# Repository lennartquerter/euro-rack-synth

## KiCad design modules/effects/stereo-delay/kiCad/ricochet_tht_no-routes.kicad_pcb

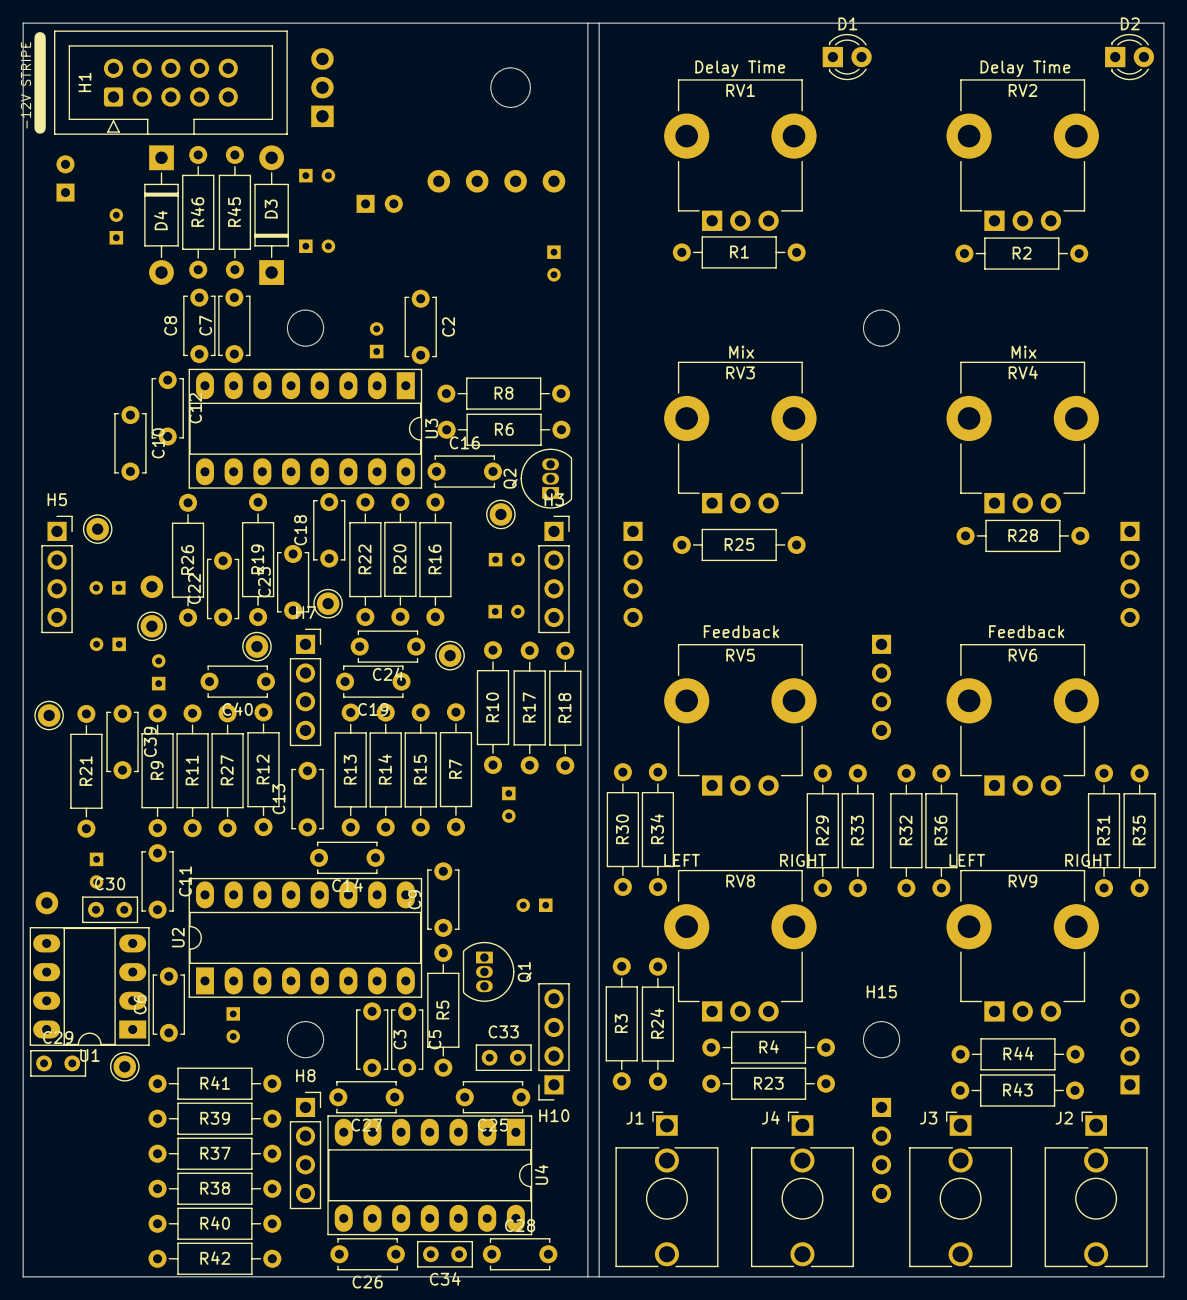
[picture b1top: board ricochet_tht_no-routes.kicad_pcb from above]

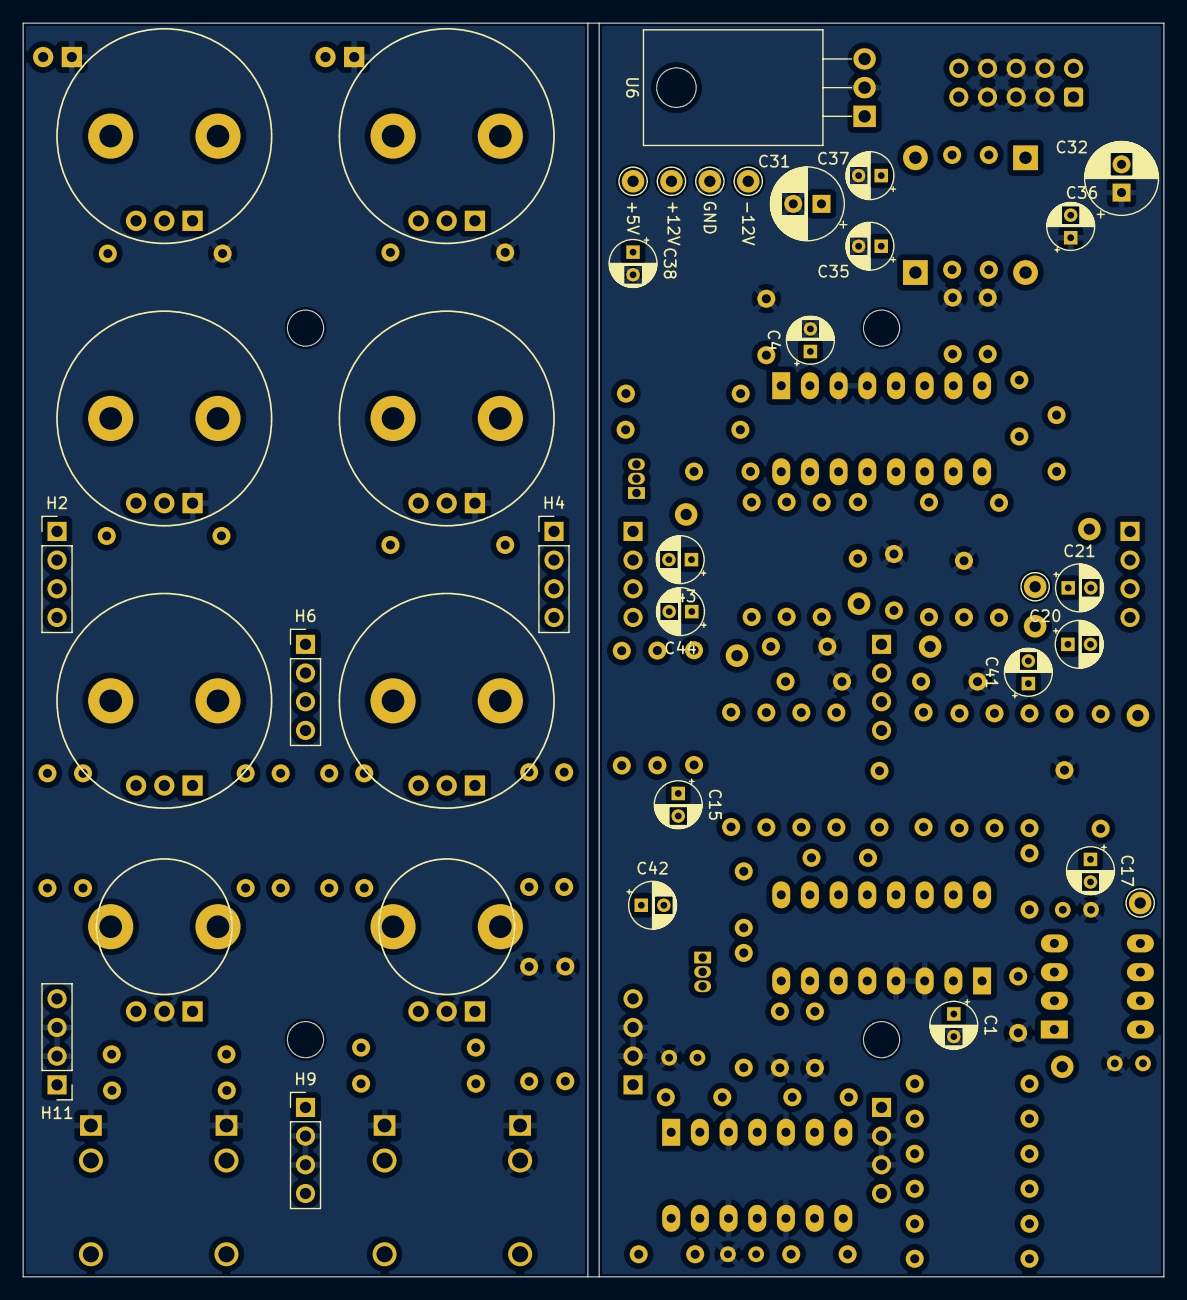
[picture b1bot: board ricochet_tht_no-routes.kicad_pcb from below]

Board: 2 copper layers, 101.0 x 111.0 mm, 142 parts (28 on the bottom side), 96 nets, no tracks yet.

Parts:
C1, C4, C21, C41, C42, C43: 10uF; CP_Radial_D4.0mm_P2.00mm
C2, C3, C5, C6, C7, C8, C9, C10, C12, C14: 100nF; C_Disc_D5.0mm_W2.5mm_P5.00mm
C11, C13, C16, C18: 560pF; C_Disc_D5.0mm_W2.5mm_P5.00mm
C15, C17, C20, C44: 4.7uF; CP_Radial_D4.0mm_P2.00mm
C19, C22: 3.3nF; C_Disc_D5.0mm_W2.5mm_P5.00mm
C23, C40: 10nF; C_Disc_D5.0mm_W2.5mm_P5.00mm
C24, C39: 3.9nF; C_Disc_D5.0mm_W2.5mm_P5.00mm
C25, C26: 27pF; C_Disc_D5.0mm_W2.5mm_P5.00mm
C27, C28: 47pF; C_Disc_D5.0mm_W2.5mm_P5.00mm
C29, C30, C33, C34: 0.1uF; C_Rect_L4.6mm_W2.0mm_P2.50mm_MKS02_FKP02
C31, C32: 47uF; CP_Radial_D6.3mm_P2.50mm
C35, C36, C37, C38: 0.1uF; CP_Radial_D4.0mm_P2.00mm
D1, D2: LED; LED_D3.0mm
D3, D4: 1N5819; D_DO-41_SOD81_P10.16mm_Horizontal
H1: Conn_02x05_PWR_Eurorack; IDC-Header_2x05_P2.54mm_Vertical
H2, H4, H6, H9, H11: PinHeader_01x04; PinHeader_1x04_P2.54mm_Vertical
H3, H5, H7, H8, H10: PinSocket_01x04; PinSocket_1x04_P2.54mm_Vertical
H12, H13, H14, H15: MountingHole; MountingHole_3.2mm_M3
J1, J4: INPUT; Jack_3.5mm_QingPu_WQP-PJ398SM_Vertical_CircularHoles
J2: L/MONO_OUTPUT; Jack_3.5mm_QingPu_WQP-PJ398SM_Vertical_CircularHoles
J3: R_OUTPUT; Jack_3.5mm_QingPu_WQP-PJ398SM_Vertical_CircularHoles
Q1, Q2: 2N3904; TO-92_Inline
R1, R2: 2K; R_Default (DIN0207)
R3, R7, R8, R24: 100K; R_Default (DIN0207)
R4, R5, R6, R23, R43, R44: 1K; R_Default (DIN0207)
R9, R11, R14, R15, R16, R17, R22, R25, R26, R28, R29, R30, R31, R32, R33, R34, R35, R36, R39, R40, R41, R42: 10K; R_Default (DIN0207)
R10, R13, R20, R21: 15K; R_Default (DIN0207)
R12, R19: 5.6K; R_Default (DIN0207)
R18, R27: 4.7K; R_Default (DIN0207)
R37, R38: 33K; R_Default (DIN0207)
R45, R46: 10R; R_Default (DIN0207)
RV1, RV2: B50K; Potentiometer_TT_P0915N
RV3, RV4, RV5, RV6: B100K; Potentiometer_TT_P0915N
RV8, RV9: B25K; Potentiometer_TT_P0915N
TP1: +12V; Pin_D1.0mm_L10.0mm
TP2: GND; Pin_D1.0mm_L10.0mm
TP3: -12V; Pin_D1.0mm_L10.0mm
TP4: INPUT_CH_1; Pin_D1.0mm_L10.0mm
TP5: INPUT_CH_2; Pin_D1.0mm_L10.0mm
TP6: OUTPUT_CH_1; Pin_D1.0mm_L10.0mm
TP7: OUTPUT_CH_2; Pin_D1.0mm_L10.0mm
TP8: DELAY_TIME_CH_2; Pin_D1.0mm_L10.0mm
TP9: DELAY_TIME_CH_1; Pin_D1.0mm_L10.0mm
TP10: POST_FEEDBACK_CH_2; Pin_D1.0mm_L10.0mm
TP11: POST_FEEDBACK_CH_1; Pin_D1.0mm_L10.0mm
TP12: MIX_INPUT_CH_2; Pin_D1.0mm_L10.0mm
TP13: MIX_INPUT_CH_1; Pin_D1.0mm_L10.0mm
TP14: +5V; Pin_D1.0mm_L10.0mm
U1: TL072; DIP-8_W7.62mm_Socket_LongPads
U2, U3: PT2399; DIP-16_W7.62mm_Socket_LongPads
U4: TL074; DIP-14_W7.62mm_Socket_LongPads
U6: L7805; TO-220-3_Horizontal_TabDown

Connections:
+5V: C2.2, C6.2, C38.1, TP14.1, U2.1 (VCC), U3.1 (VCC), U6.3 (OUT)
+12V: C29.1, C31.1, C33.1, C35.1, C37.1, R7.2, R8.2, R45.2, TP1.1, U1.8 (V+), U4.4 (V+), U6.1 (IN)
-12V: C30.2, C32.2, C34.2, C36.2, R46.2, TP3.1, U1.4 (V-), U4.11 (V-)
/PT2399_delay-module_channel_1/delay_input: C15.2, TP4.1, U1.1, U1.2 (-)
/PT2399_delay-module_channel_1/delay_output: C42.2, H7.2, TP6.1
/PT2399_delay-module_channel_2/delay_input: C17.2, TP5.1, U1.6 (-), U1.7
/PT2399_delay-module_channel_2/delay_output: C41.2, H7.1, TP7.1
GNDREF: C1.2, C2.1, C3.2, C4.2, C5.2, C6.1, C7.2, C8.2, C19.2, C22.2, C23.2, C24.2, C29.2, C30.1, C31.2, C32.1, C33.2, C34.1, C35.2, C36.1, C37.2, C38.2, C39.2, C40.2, D1.1 (K), D2.1 (K), H1.3, H1.4, H1.5, H1.6, H1.7, H1.8, H8.2, H8.3, H9.2, H9.3, H10.2, H10.3, H11.2, H11.3, J1.S, J1.TN, J2.S, J3.S, J4.S, R1.1, R2.1, R3.1, R24.1, RV3.1, RV4.1, RV8.2, RV9.2, TP2.1, U2.3 (AGND), U2.4 (DGND), U3.3 (AGND), U3.4 (DGND), U4.3 (+), U4.5 (+), U4.10 (+), U4.12 (+), U6.2 (GND)
unnamed: C15.1, R10.1
unnamed: C17.1, R21.1
unnamed: C19.1, R13.2, R14.2, R15.2
unnamed: C20.1, C39.1, R9.2, R11.2, R21.2, TP10.1
unnamed: C21.1, C40.1, R12.2, TP12.1
unnamed: C22.1, R20.2, R22.2, R26.2
unnamed: C23.1, C43.1, R19.2, TP13.1
unnamed: C24.1, C44.1, R10.2, R16.2, R17.2, TP11.1
unnamed: C25.2, R37.2, R39.1, U4.1
unnamed: C26.2, R38.2, R40.1, U4.8
unnamed: C41.1, R27.2
unnamed: C42.1, R18.2
unnamed: D1.2 (A), H4.2
unnamed: D2.2 (A), H2.2
unnamed: D3.2 (A), H1.9, H1.10
unnamed: D3.1 (K), R45.1
unnamed: D4.2 (A), R46.1
unnamed: D4.1 (K), H1.1, H1.2
unnamed: H2.1, RV2.1
unnamed: H2.3, RV4.3
unnamed: H2.4, RV6.2
unnamed: H3.1, TP9.1, U3.6 (VCO)
unnamed: H3.2, Q2.1 (E)
unnamed: C43.2, H3.3
unnamed: C44.2, H3.4
unnamed: H4.1, RV1.1
unnamed: H4.3, RV3.3
unnamed: H4.4, RV5.2
unnamed: H5.1, TP8.1, U2.6 (VCO)
unnamed: H5.2, Q1.1 (E)
unnamed: C21.2, H5.3
unnamed: C20.2, H5.4
unnamed: H6.1, R31.1, R32.1
unnamed: H6.2, R29.1, R30.1
unnamed: H6.3, R34.2, R36.2
unnamed: H6.4, R33.2, R35.2
unnamed: C26.1, H7.3, R38.1, U4.9 (-)
unnamed: C25.1, H7.4, R37.1, U4.2 (-)
unnamed: H8.1, U1.3 (+)
unnamed: H8.4, U1.5 (+)
unnamed: H9.1, R4.1
unnamed: H9.4, R23.1
unnamed: C27.2, H10.1, R41.2, U4.7
unnamed: C28.2, H10.4, R42.2, U4.14
unnamed: H11.1, R43.2
unnamed: H11.4, R44.2
unnamed: J1.T, J4.TN, R3.2, R4.2
unnamed: J2.T, J3.TN, R43.1
unnamed: J3.T, R44.1
unnamed: J4.T, R23.2, R24.2
unnamed: Q1.2 (B), R5.2
unnamed: Q1.3 (C), R7.1
unnamed: Q2.2 (B), R6.2
unnamed: Q2.3 (C), R8.1
unnamed: R1.2, RV1.2, RV1.3
unnamed: R2.2, RV2.2, RV2.3
unnamed: R25.1, RV5.3
unnamed: R25.2, RV3.2
unnamed: R28.1, RV6.3
unnamed: R28.2, RV4.2
unnamed: R29.2, R33.1, RV8.3
unnamed: R30.2, R34.1, RV8.1
unnamed: R31.2, R35.1, RV9.3
unnamed: R32.2, R36.1, RV9.1
unnamed: C5.1, R5.1, U2.8 (CC0)
unnamed: C3.1, U2.7 (CC1)
unnamed: C11.1, R9.1, U2.16 (LPF1-IN)
unnamed: C11.2, R11.1, R27.1, U2.15 (LPF1-OUT)
unnamed: C13.2, R14.1, U2.13 (LPF2-IN)
unnamed: C13.1, R12.1, R13.1, U2.14 (LPF2-OUT)
unnamed: C9.1, U2.10 (OP1-IN)
unnamed: C9.2, U2.9 (OP1-OUT)
unnamed: C14.1, U2.11 (OP2-IN)
unnamed: C14.2, R15.1, U2.12 (OP2-OUT)
unnamed: C1.1, U2.2 (REF)
unnamed: C8.1, R6.1, U3.8 (CC0)
unnamed: C7.1, U3.7 (CC1)
unnamed: C16.1, R16.1, U3.16 (LPF1-IN)
unnamed: C16.2, R17.1, R18.1, U3.15 (LPF1-OUT)
unnamed: C18.2, R22.1, U3.13 (LPF2-IN)
unnamed: C18.1, R19.1, R20.1, U3.14 (LPF2-OUT)
unnamed: C12.1, U3.10 (OP1-IN)
unnamed: C12.2, U3.9 (OP1-OUT)
unnamed: C10.1, U3.11 (OP2-IN)
unnamed: C10.2, R26.1, U3.12 (OP2-OUT)
unnamed: C4.1, U3.2 (REF)
unnamed: C27.1, R39.2, R41.1, U4.6 (-)
unnamed: C28.1, R40.2, R42.1, U4.13 (-)

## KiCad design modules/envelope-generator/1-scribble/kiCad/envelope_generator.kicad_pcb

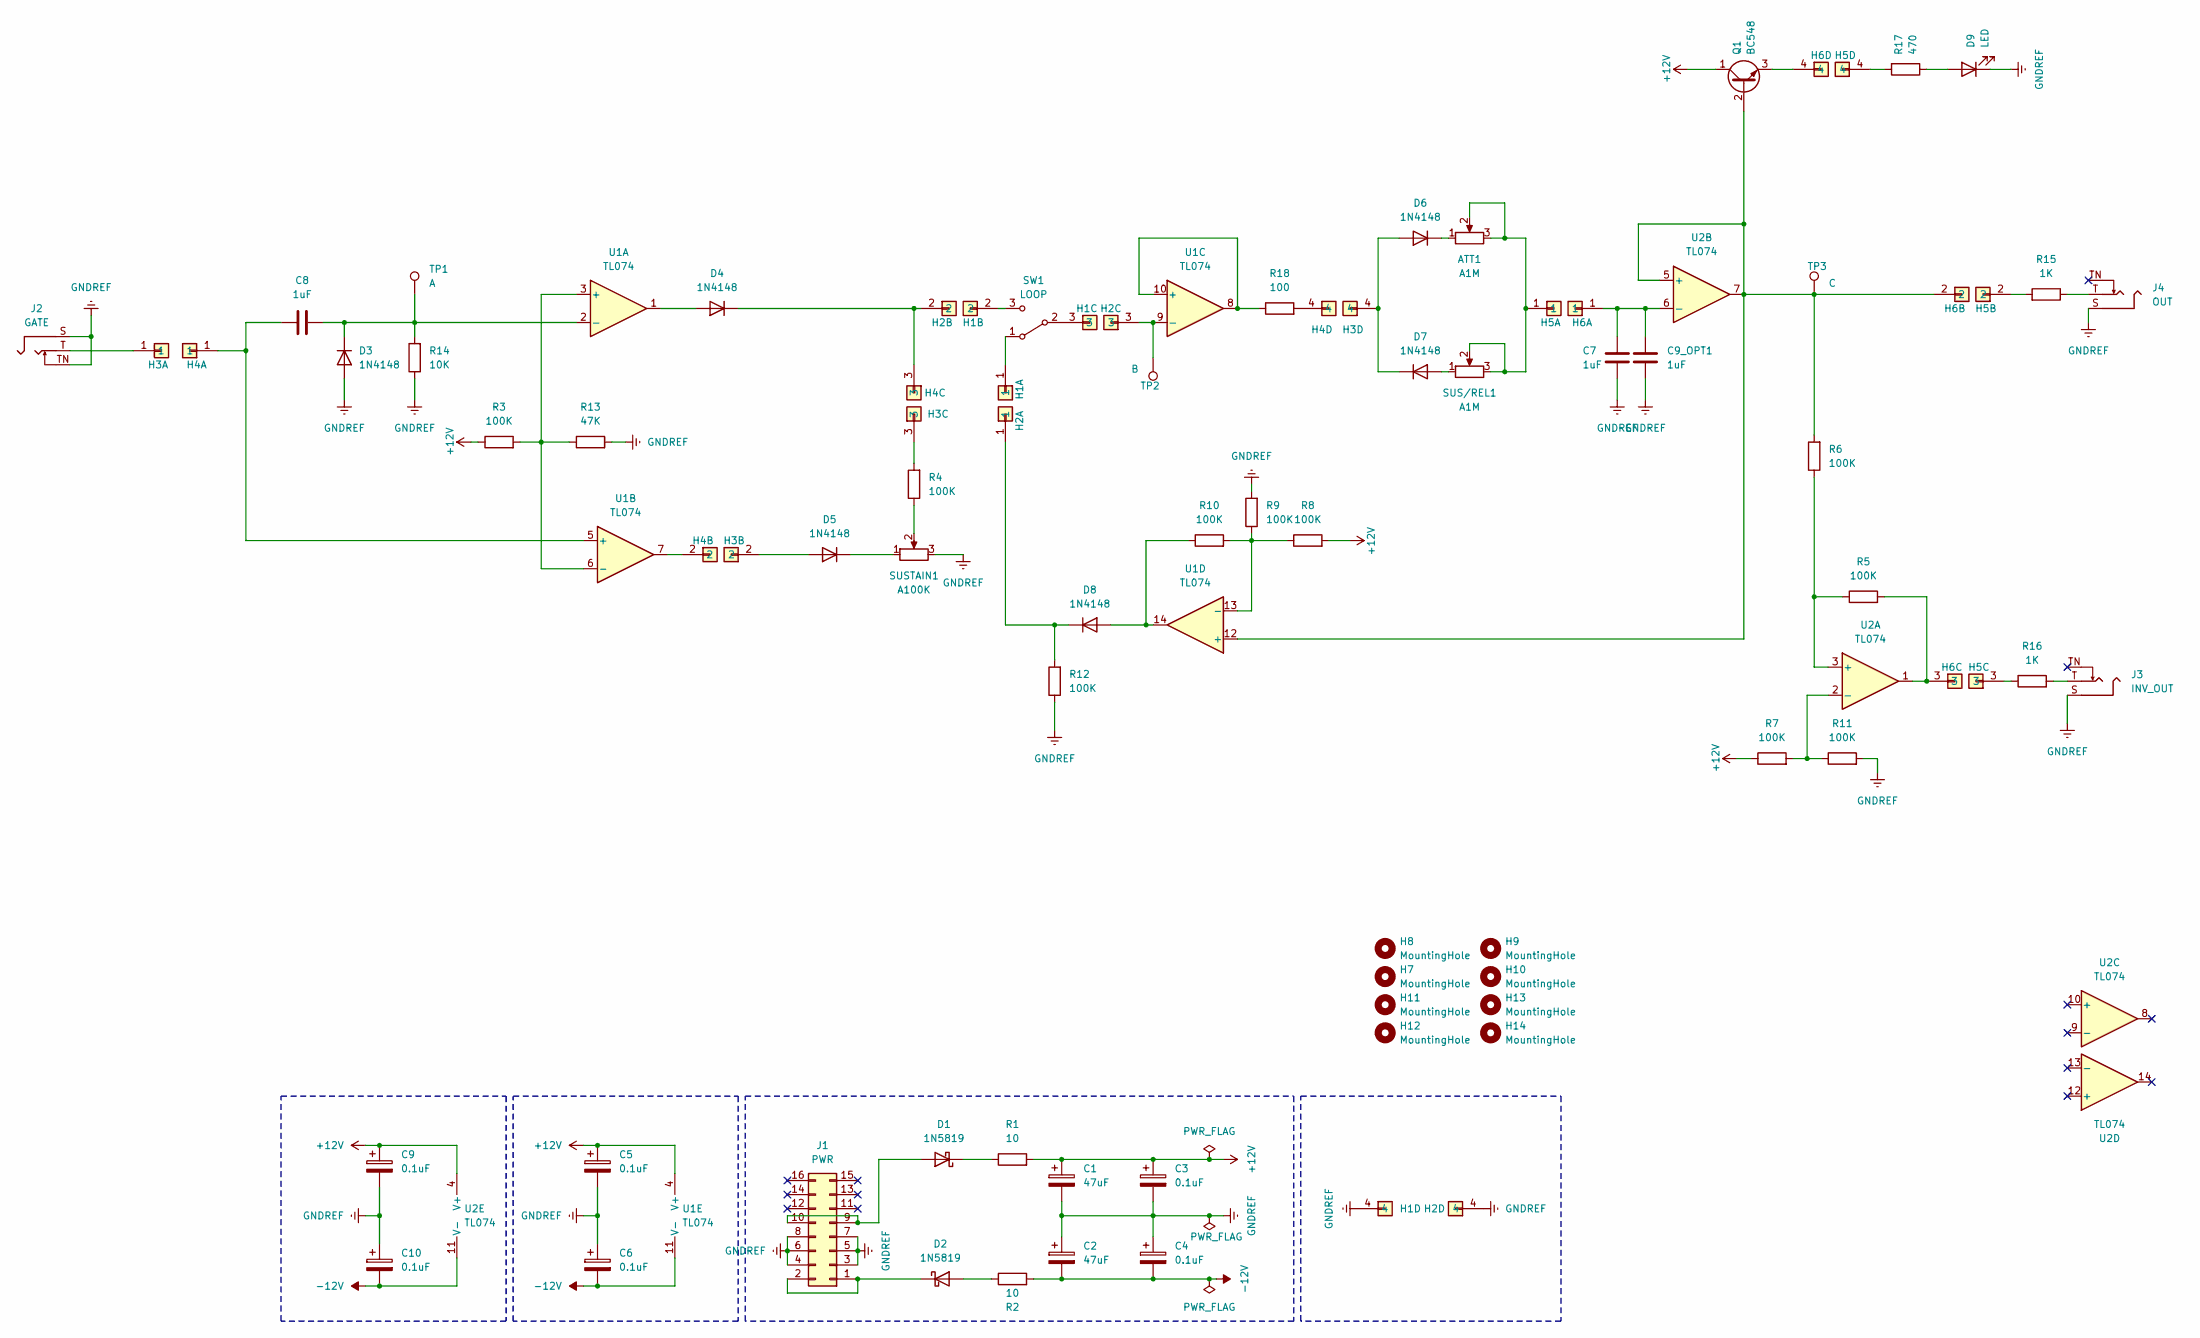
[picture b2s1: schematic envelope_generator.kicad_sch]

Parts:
ATT1: A1M; Potentiometer_TT_P0915N
C1, C2: 47uF; CP_Radial_D6.3mm_P2.50mm
C3, C4, C5, C6, C9, C10: 0.1uF; CP_Radial_D4.0mm_P2.00mm
C7, C8, C9_OPT1: 1uF; C_RECT_MKT_1uF
D1, D2: 1N5819; D_DO-41_SOD81_P10.16mm_Horizontal
D3, D4, D5, D6, D7, D8: 1N4148; D_DO-35_SOD27_P7.62mm_Horizontal
D9: LED; LED_D3.0mm
H1: PinHeader_1x04_P2.00mm_Vertical
H2: PinSocket_1x04_P2.00mm_Vertical
H3: TOP_8_SGL; PinHeader_1x04_P2.00mm_Vertical
H4, H6: BTM_8_SGL; PinSocket_1x04_P2.00mm_Vertical
H5: BTM_8_SGL; PinHeader_1x04_P2.00mm_Vertical
H7, H8, H9, H10, H11, H12, H13, H14: MountingHole; MountingHole_2.5mm
J1: PWR; CONN_02x08_PWR
J2: GATE; Jack_3.5mm_QingPu_WQP-PJ398SM_Vertical_CircularHoles
J3: INV_OUT; Jack_3.5mm_QingPu_WQP-PJ398SM_Vertical_CircularHoles
J4: OUT; Jack_3.5mm_QingPu_WQP-PJ398SM_Vertical_CircularHoles
Q1: BC548; TO-92_Inline
R1, R2: 10; R_Axial_DIN0207_L6.3mm_D2.5mm_P7.62mm_Horizontal
R3, R4, R5, R6, R7, R8, R9, R10, R11, R12: 100K; R_Axial_DIN0207_L6.3mm_D2.5mm_P7.62mm_Horizontal
R13: 47K; R_Axial_DIN0207_L6.3mm_D2.5mm_P7.62mm_Horizontal
R14: 10K; R_Axial_DIN0207_L6.3mm_D2.5mm_P7.62mm_Horizontal
R15, R16: 1K; R_Axial_DIN0207_L6.3mm_D2.5mm_P7.62mm_Horizontal
R17: 470; R_Axial_DIN0207_L6.3mm_D2.5mm_P7.62mm_Horizontal
R18: 100; R_Axial_DIN0207_L6.3mm_D2.5mm_P7.62mm_Horizontal
SUS/REL1: A1M; Potentiometer_TT_P0915N
SUSTAIN1: A100K; Potentiometer_TT_P0915N
SW1: LOOP; SPDT_Toggle
TP1: A
TP2: B
TP3: C
U1, U2: TL074; DIP-14_W7.62mm_Socket_LongPads

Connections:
+12V: C1.1, C3.1, C5.1, C9.1, Q1.1 (C), R1.2, R3.1, R7.1, R8.2, U1.4 (V+), U2.4 (V+)
-12V: C2.2, C4.2, C6.2, C10.2, R2.2, U1.11 (V-), U2.11 (V-)
GNDREF: C1.2, C2.1, C3.2, C4.1, C5.2, C6.1, C7.2, C9.2, C9_OPT1.2, C10.1, D3.2 (A), D9.1 (K), H1.4, H2.4, J1.3 (GND), J1.4 (GND), J1.5 (GND), J1.6 (GND), J1.7 (GND), J1.8 (GND), J2.S, J2.TN, J3.S, J4.S, R9.2, R11.2, R12.1, R13.2, R14.1, SUSTAIN1.3
unnamed: ATT1.2, ATT1.3, H5.1, SUS/REL1.2, SUS/REL1.3
unnamed: D1.2 (A), J1.9 (+12V), J1.10 (+12V)
unnamed: D1.1 (K), R1.1
unnamed: D2.2 (A), R2.1
unnamed: D2.1 (K), J1.1 (-12V), J1.2 (-12V)
unnamed: C8.2, D3.1 (K), R14.2, TP1.1, U1.2 (-)
unnamed: D4.2 (A), U1.1
unnamed: D4.1 (K), H2.2, H4.3
unnamed: D5.2 (A), H3.2
unnamed: D5.1 (K), SUSTAIN1.1
unnamed: D6.2 (A), D7.1 (K), H3.4
unnamed: ATT1.1, D6.1 (K)
unnamed: D7.2 (A), SUS/REL1.1
unnamed: D8.2 (A), R10.1, U1.14
unnamed: D8.1 (K), H2.1, R12.2
unnamed: D9.2 (A), R17.1
unnamed: H3.1, J2.T
unnamed: H3.3, R4.2
unnamed: H4.2, U1.7
unnamed: H4.4, R18.2
unnamed: H5.2, R15.2
unnamed: H5.3, R16.1
unnamed: H5.4, R17.2
unnamed: H6.3, R5.2, U2.1
unnamed: J3.T, R16.2
unnamed: J4.T, R15.1
unnamed: H6.2, Q1.2 (B), R6.2, TP3.1, U1.12 (+), U2.5 (+), U2.7
unnamed: H6.4, Q1.3 (E)
unnamed: R4.1, SUSTAIN1.2
unnamed: H1.1, SW1.1 (A)
unnamed: H1.3, SW1.2 (B)
unnamed: H1.2, SW1.3 (C)
unnamed: R3.2, R13.1, U1.3 (+), U1.6 (-)
unnamed: C8.1, H4.1, U1.5 (+)
unnamed: R18.1, U1.8, U1.10 (+)
unnamed: H2.3, TP2.1, U1.9 (-)
unnamed: R8.1, R9.1, R10.2, U1.13 (-)
unnamed: R5.1, R6.1, U2.3 (+)
unnamed: R7.2, R11.1, U2.2 (-)
unnamed: C7.1, C9_OPT1.1, H6.1, U2.6 (-)

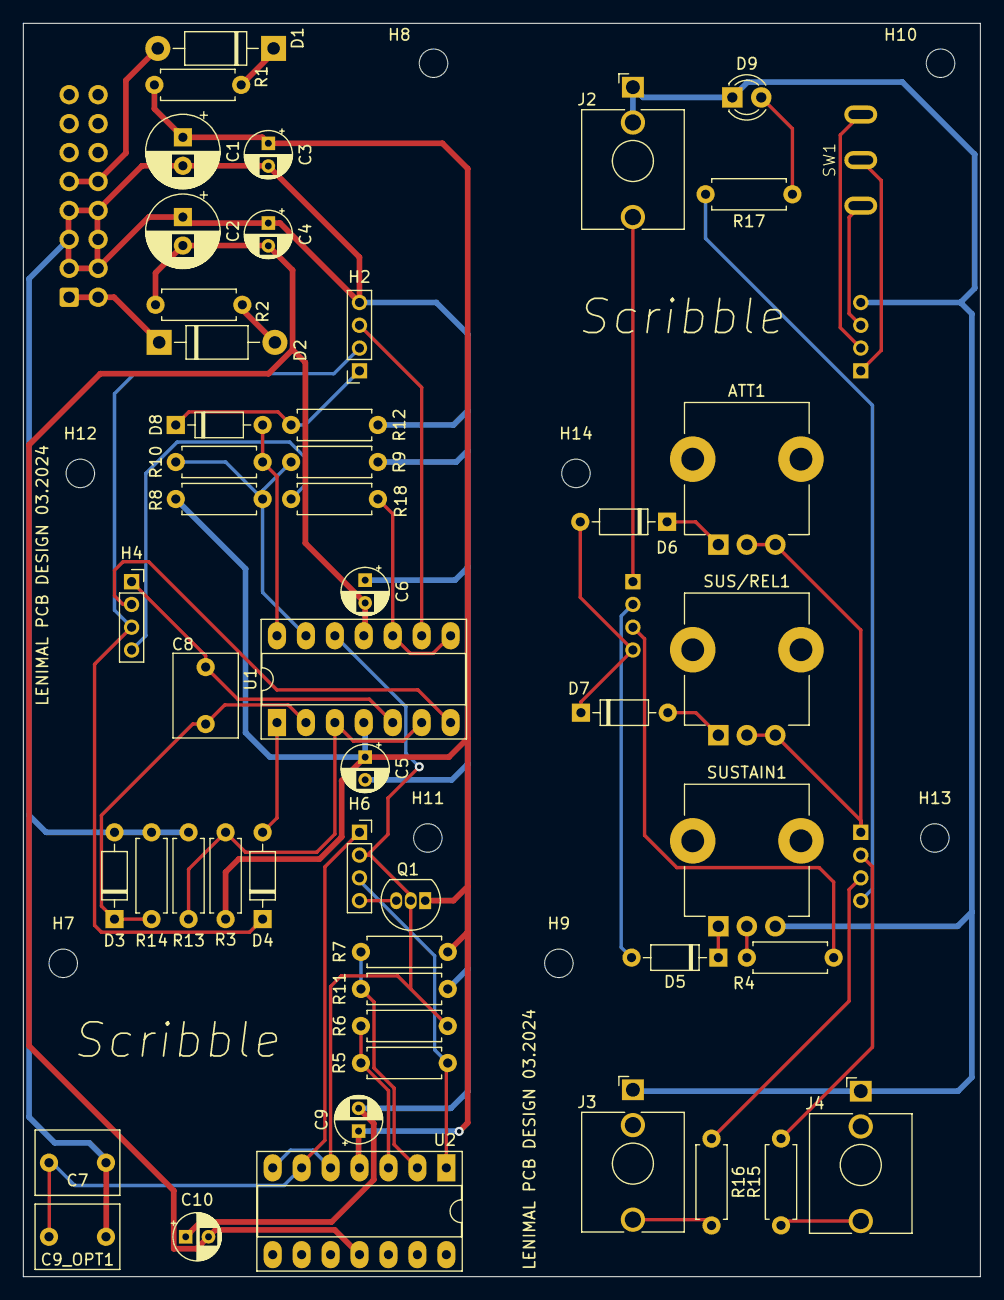
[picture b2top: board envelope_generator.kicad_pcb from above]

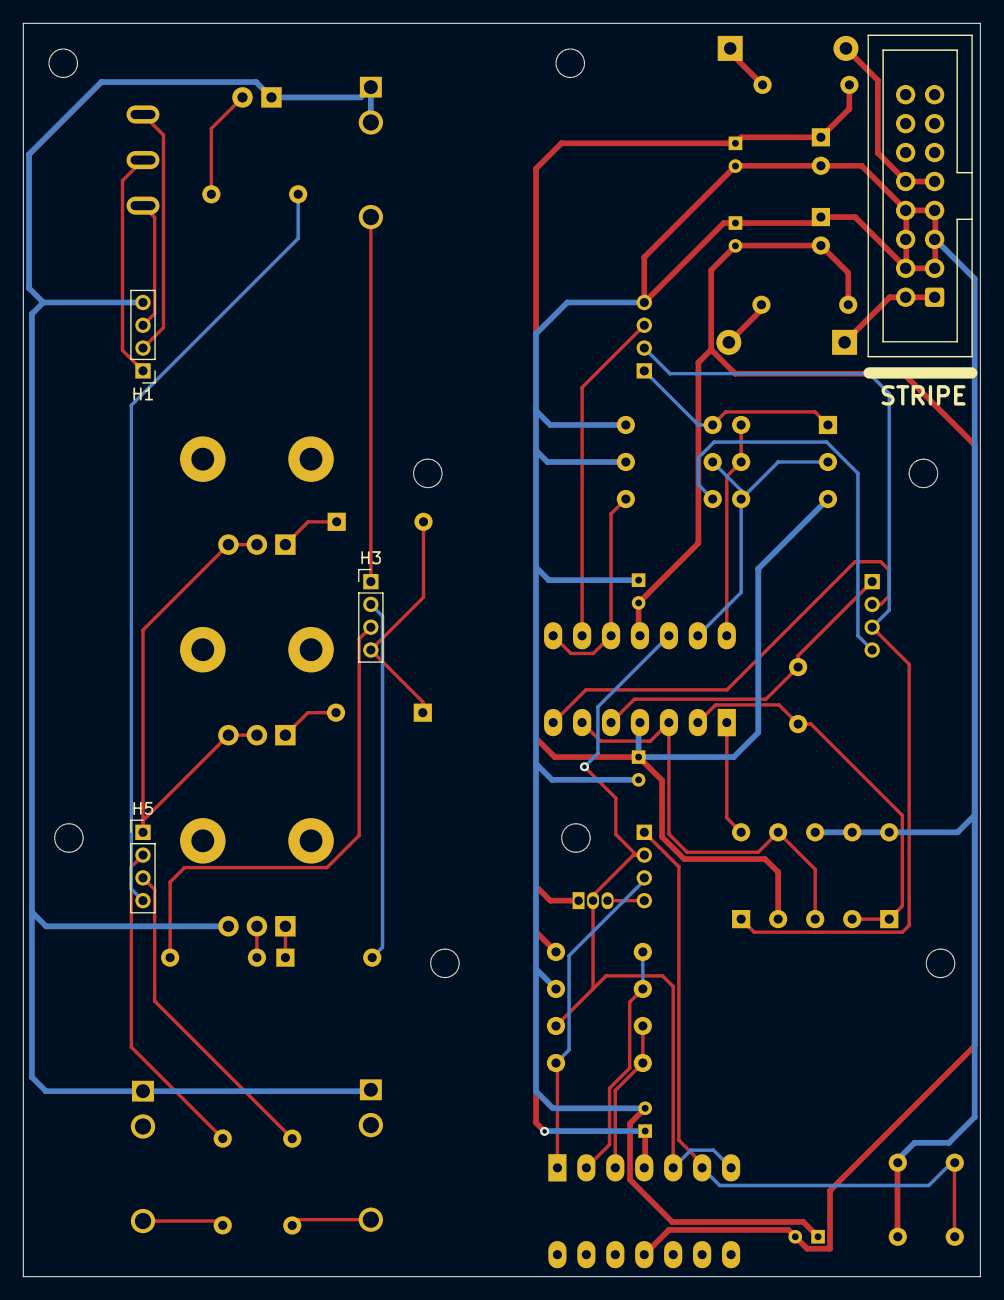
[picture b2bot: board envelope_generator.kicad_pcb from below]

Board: 2 copper layers, 84.0 x 110.0 mm, 63 parts (4 on the bottom side), 43 nets.

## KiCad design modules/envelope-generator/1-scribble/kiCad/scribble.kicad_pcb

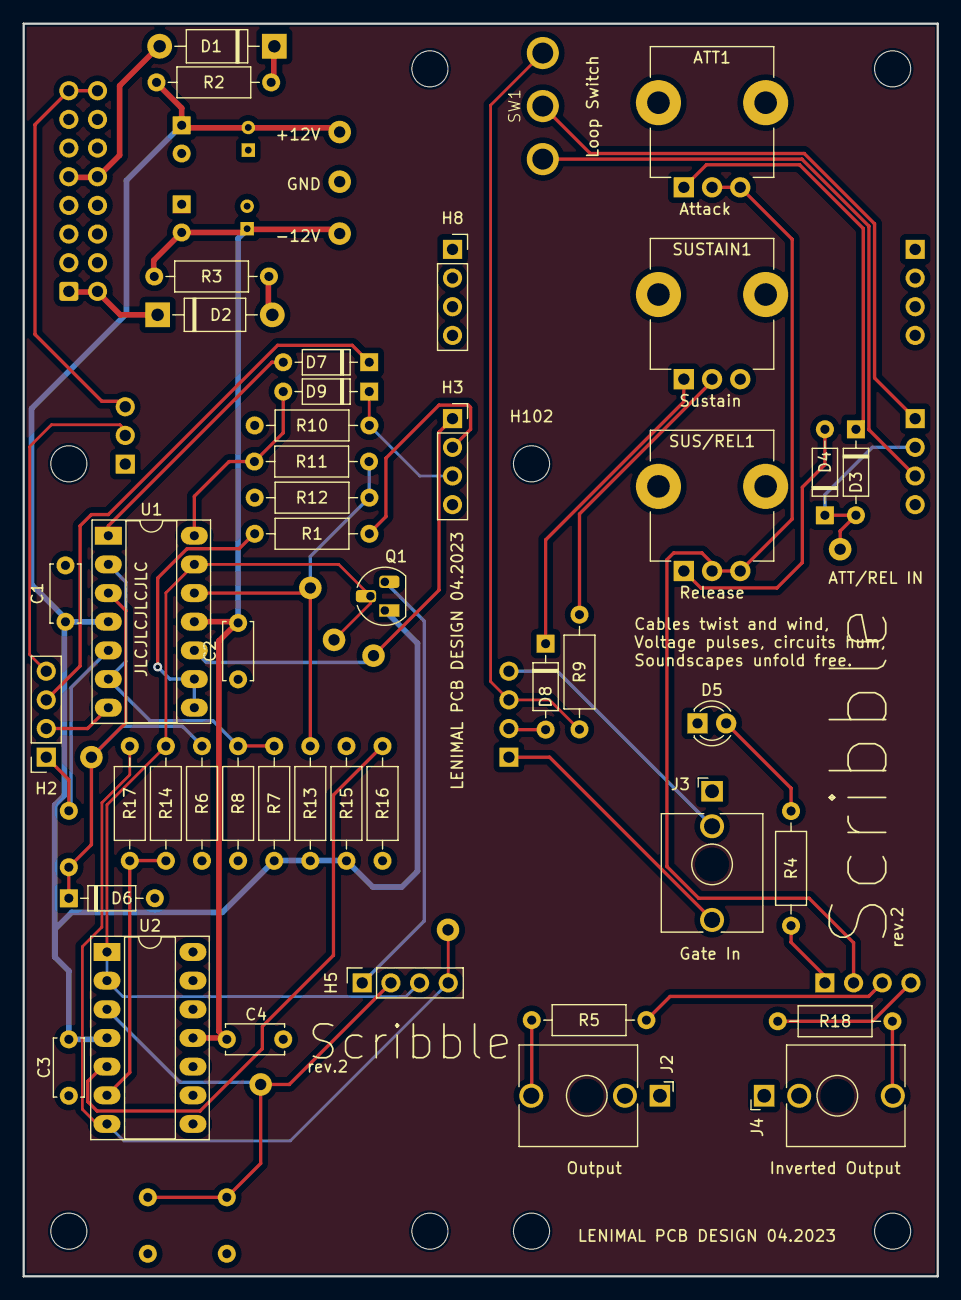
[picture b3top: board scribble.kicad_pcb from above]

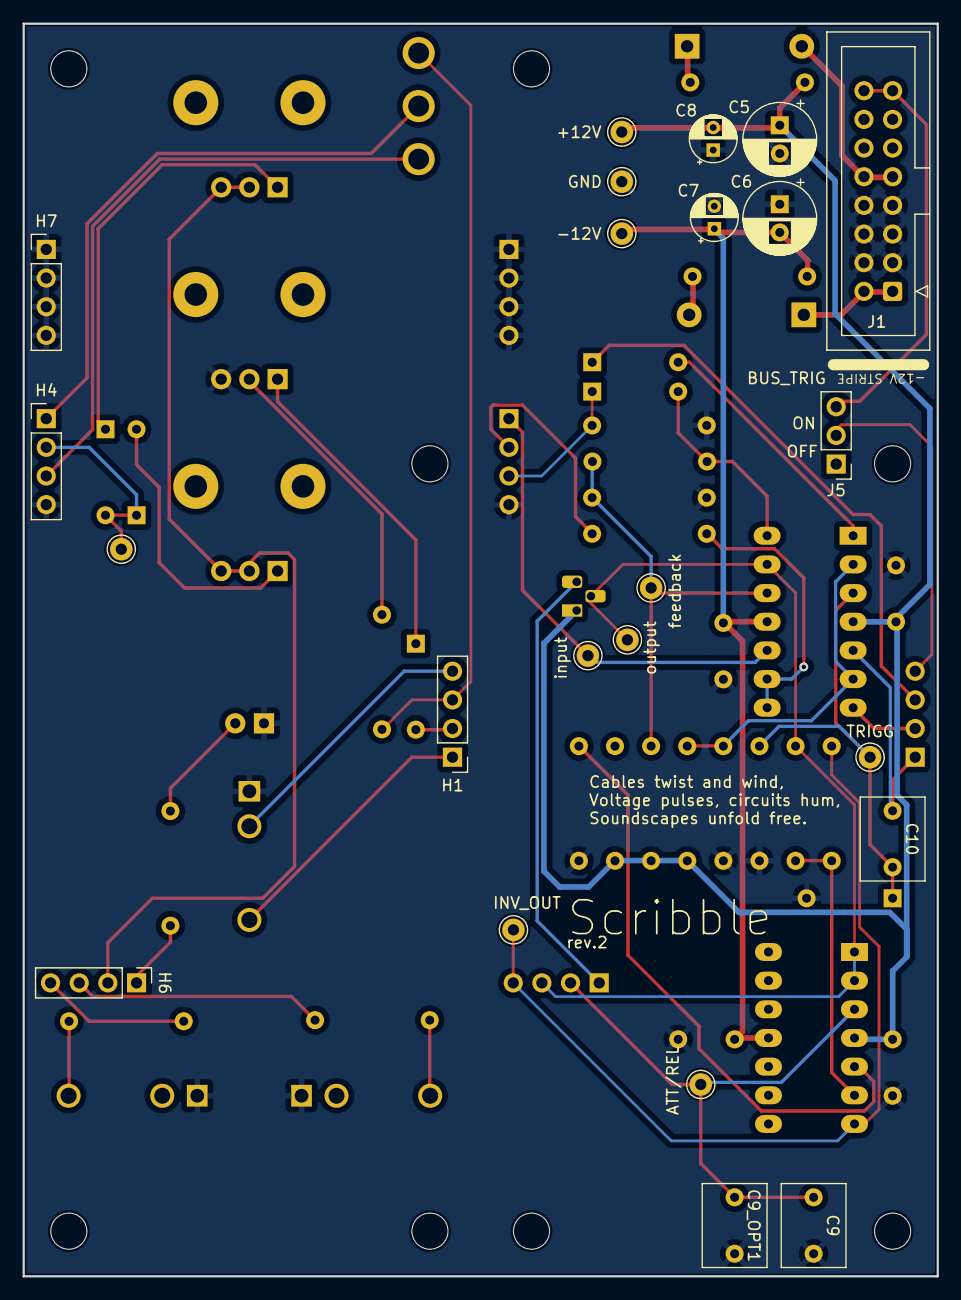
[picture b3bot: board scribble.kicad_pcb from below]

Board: 2 copper layers, 81.0 x 111.0 mm, 76 parts (23 on the bottom side), 45 nets.

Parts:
ATT1: A1M; Potentiometer_TT_P0915N
C1, C2, C3, C4: 0.1uF; C_Disc_D5.0mm_W2.5mm_P5.00mm
C5, C6: 47uF; CP_Radial_D6.3mm_P2.50mm
C7, C8: 0.1uF; CP_Radial_D4.0mm_P2.00mm
C9, C9_OPT1, C10: 1uF; C_RECT_MKT_1uF
D1, D2: 1N5819; D_DO-41_SOD81_P10.16mm_Horizontal
D3, D4, D6, D7, D8, D9: 1N4148; D_DO-35_SOD27_P7.62mm_Horizontal
D5: LED; LED_D3.0mm
H1, H4, H6, H7: PinHeader_1x04; PinHeader_1x04_P2.54mm_Vertical
H2, H3, H5, H8: PinSocket_1x04; PinSocket_1x04_P2.54mm_Vertical
H100, H102, H103, H104, H105, H106, H107, H108: MountingHole; MountingHole_3.2mm_M3
J1: PWR; IDC-Header_2x08_P2.54mm_Vertical
J2: OUT; Jack_3.5mm_QingPu_WQP-PJ398SM_Vertical_CircularHoles
J3: GATE; Jack_3.5mm_QingPu_WQP-PJ398SM_Vertical_CircularHoles
J4: INV_OUT; Jack_3.5mm_QingPu_WQP-PJ398SM_Vertical_CircularHoles
J5: PinHeader_1x03; PinHeader_1x03_P2.54mm_Vertical
Q1: BC548; TO-92_HandSolder
R1: 100R; R_Default (DIN0207)
R2, R3: 10R; R_Default (DIN0207)
R4: 470R; R_Default (DIN0207)
R5, R18: 1K; R_Default (DIN0207)
R6: 10K; R_Default (DIN0207)
R7, R9, R10, R11, R12, R13, R14, R15, R16, R17: 100K; R_Default (DIN0207)
R8: 47K; R_Default (DIN0207)
SUS/REL1: A1M; Potentiometer_TT_P0915N
SUSTAIN1: A100K; Potentiometer_TT_P0915N
SW1: LOOP; SW_default
TP1: TRG_INPUT; Pin_D1.0mm_L10.0mm
TP2: OUT; Pin_D1.0mm_L10.0mm
TP3: TRG; Pin_D1.0mm_L10.0mm
TP4: FBCK_VD; Pin_D1.0mm_L10.0mm
TP5, TP6, TP7: C; Pin_D1.0mm_L10.0mm
TP8: CAP_OUT; Pin_D1.0mm_L10.0mm
TP9: CAP_IN; Pin_D1.0mm_L10.0mm
TP10: INV_OUT; Pin_D1.0mm_L10.0mm
U1, U2: TL074; DIP-14_W7.62mm_Socket_LongPads

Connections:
+12V: C1.1, C3.1, C5.1, C7.1, Q1.1 (C), R2.1, R7.2, R13.1, R15.2, TP5.1, U1.4 (V+), U2.4 (V+)
-12V: C2.2, C4.2, C6.2, C8.2, R3.1, TP7.1, U1.11 (V-), U2.11 (V-)
/feedback_loop/feedback_input: H5.3, Q1.2 (B), R14.1, TP2.1, U1.13 (-), U2.1, U2.2 (-)
/feedback_loop/feedback_output: D9.1 (K), H3.3, R10.1
/input_sustain/gate_in: H2.4, J5.2
/input_sustain/gate_out: H1.3, R9.1, SW1.3 (C)
/inverted_out/inv_output: H5.4, R17.1, TP10.1, U2.7
GNDREF: C1.2, C2.1, C3.2, C4.1, C5.2, C6.1, C7.2, C8.1, C9.2, C9_OPT1.2, D5.1 (K), D6.2 (A), H3.4, H4.4, H7.1, H7.2, H7.3, H7.4, H8.1, H8.2, H8.3, H8.4, J1.3 (GND), J1.4 (GND), J1.5 (GND), J1.6 (GND), J1.7 (GND), J1.8 (GND), J2.S, J3.S, J4.S, R6.2, R8.1, R10.2, R12.1, R16.1, SUSTAIN1.3, TP6.1
unnamed: D1.2 (A), J1.9 (+12V), J1.10 (+12V)
unnamed: D1.1 (K), R2.2
unnamed: D2.2 (A), R3.2
unnamed: D2.1 (K), J1.1 (-12V), J1.2 (-12V)
unnamed: D3.2 (A), D4.1 (K), H4.2, TP9.1
unnamed: ATT1.1, D3.1 (K)
unnamed: D4.2 (A), SUS/REL1.1
unnamed: D5.2 (A), R4.2
unnamed: C10.2, D6.1 (K), R6.1, TP3.1, U1.3 (+)
unnamed: D7.2 (A), U1.1
unnamed: D7.1 (K), H2.3
unnamed: D8.2 (A), H1.2
unnamed: D8.1 (K), SUSTAIN1.1
unnamed: D9.2 (A), R11.2, U1.14
unnamed: H1.1, J3.T
unnamed: H1.4, J3.TN
unnamed: C10.1, H2.1, U1.5 (+)
unnamed: H2.2, U1.7
unnamed: H3.1, TP1.1, U1.10 (+)
unnamed: H3.2, R1.1
unnamed: H4.1, SW1.2 (B)
unnamed: H4.3, SW1.1 (A)
unnamed: H5.1, Q1.3 (E)
unnamed: C9.1, C9_OPT1.1, H5.2, TP8.1, U2.3 (+)
unnamed: H6.1, R4.1
unnamed: ATT1.2, ATT1.3, H6.2, SUS/REL1.2, SUS/REL1.3
unnamed: H6.3, R5.1
unnamed: H6.4, R18.2
unnamed: J2.T, R5.2
unnamed: J4.T, R18.1
unnamed: J1.15 (GATE), J1.16 (GATE), J5.3
unnamed: R9.2, SUSTAIN1.2
unnamed: R7.1, R8.2, U1.2 (-), U1.6 (-)
unnamed: R1.2, U1.8, U1.9 (-)
unnamed: R11.1, R12.2, R13.2, TP4.1, U1.12 (+)
unnamed: R15.1, R16.2, U2.5 (+)
unnamed: R14.2, R17.2, U2.6 (-)

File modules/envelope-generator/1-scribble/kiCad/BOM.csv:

"Reference","Value","Datasheet","Footprint","Qty","DNP"
"ATT1,SUS/REL1","A1M","~","Synth:Potentiometer_TT_P0915N","2",""
"C1,C2,C3,C4,C7,C8","0.1uF","~","Capacitor_THT:CP_Radial_D4.0mm_P2.00mm","6",""
"C5,C6","47uF","~","Capacitor_THT:CP_Radial_D6.3mm_P2.50mm","2",""
"C9,C9_OPT1,C10","1uF","~","Synth:C_RECT_MKT_1uF","3",""
"D1,D2","1N5819","http://www.vishay.com/docs/88525/1n5817.pdf","Synth:D_DO-41_SOD81_P10.16mm_Horizontal","2",""
"D3,D4,D6,D7,D8,D9","1N4148","https://assets.nexperia.com/documents/data-sheet/1N4148_1N4448.pdf","Synth:D_DO-35_SOD27_P7.62mm_Horizontal","6",""
"D5","LED","~","LED_THT:LED_D3.0mm","1",""
"H1","TOP_IN","~","-- mixed values --","1",""
"H2","BTM_IN","~","-- mixed values --","1",""
"H3","BTM_SW","~","Synth:PinSocket_1x04_P2.54mm_Vertical","1",""
"H4","TOP_SW","~","Synth:PinHeader_1x04_P2.54mm_Vertical","1",""
"H5","BTM_OUT","~","Synth:PinSocket_1x04_P2.54mm_Vertical","1",""
"H6","TOP_OUT","~","Synth:PinHeader_1x04_P2.54mm_Vertical","1",""
"H7","TOP_PWR","~","Synth:PinHeader_1x04_P2.54mm_Vertical","1",""
"H8","BTM_PWR","~","Synth:PinSocket_1x04_P2.54mm_Vertical","1",""
"H100,H102,H103,H104,H105,H106,H107,H108","MountingHole","~","MountingHole:MountingHole_3.2mm_M3","8",""
"J1","PWR","~","Synth:IDC-Header_2x08_P2.54mm_Vertical","1",""
"J2,TP2","OUT","~","-- mixed values --","2",""
"J3","GATE","~","Synth:Jack_3.5mm_QingPu_WQP-PJ398SM_Vertical_CircularHoles","1",""
"J4,TP10","INV_OUT","~","-- mixed values --","2",""
"Q1","BC548","https://www.onsemi.com/pub/Collateral/BC550-D.pdf","Package_TO_SOT_THT:TO-92_HandSolder","1",""
"R1","100","~","Synth:R_Default (DIN0207)","1",""
"R2,R3","10","~","Synth:R_Default (DIN0207)","2",""
"R4","470","~","Synth:R_Default (DIN0207)","1",""
"R5,R18","1K","~","Synth:R_Default (DIN0207)","2",""
"R6","10K","~","Synth:R_Default (DIN0207)","1",""
"R7,R9,R10,R11,R12,R13,R14,R15,R16,R17","100K","~","Synth:R_Default (DIN0207)","10",""
"R8","47K","~","Synth:R_Default (DIN0207)","1",""
"SUSTAIN1","A100K","~","Synth:Potentiometer_TT_P0915N","1",""
"SW1","LOOP","~","Synth:SW_default","1",""
"TP1","TRG_INPUT","~","Connector_Pin:Pin_D1.0mm_L10.0mm","1",""
"TP3","TRG","~","Connector_Pin:Pin_D1.0mm_L10.0mm","1",""
"TP4","FBCK_VD","~","Connector_Pin:Pin_D1.0mm_L10.0mm","1",""
"TP5,TP6,TP7","C","~","Connector_Pin:Pin_D1.0mm_L10.0mm","3",""
"TP8","CAP_OUT","~","Connector_Pin:Pin_D1.0mm_L10.0mm","1",""
"TP9","CAP_IN","~","Connector_Pin:Pin_D1.0mm_L10.0mm","1",""
"U1,U2","TL074","http://www.ti.com/lit/ds/symlink/tl071.pdf","Package_DIP:DIP-14_W7.62mm_Socket_LongPads","2",""
